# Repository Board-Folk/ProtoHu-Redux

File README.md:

# ProtoHu Redux

## A Simple flash HuCard for the NEC PC Engine/Turbo-Grafx range of consoles.

This project is based upon David Shadoff's [ProtoHu](https://github.com/dshadoff/ProtoHu_revA).
The original Eagle project was converted to KiCad. The most important
difference is the addition of an OR gate to fully decode the HuCard
address space, such that the image written to the flash is available
only in the lower half and not mirrored the the upper one. The
motivation for this is for the card to respond to the minimum practical
range of addresses in the HuCard space, freeing the upper region such
that diagnostic tests may be performed without risk of conflicts with
hardware in a real console. Specifically, this card can be flashed with
diagnostics for the CD hardware found in a PC Engine/Turb Duo system.

## PCB Production

The project consists of two boards: one that features the HuCard
connector and all the components, the other being a spacer to fit under
the first to give the complete assembly a flat lower surface. The upper
board should be 0.8mm thick with at least an ENIG finish for gold
plating on the edge connector contacts. A chamfered edge near the
connector will improve the fit.

The spacer board should be 1.6mm to clear the height of the components and
bring the total up to 2.4mm, which seems to be the nominal dimension of a
standard HuCard. As it contains no components, the finish on the spacer
boards is not important.

This visual design is intended to look vaguely like an original HuCard
when white solder mask is used with black silkscreen.

## BOM

| Reference  | Value          | Footprint |
|------------|----------------|-----------|
| C1,C3      | 0.1uF          | 0805      |
| C2         | 1uF            | 0805      |
| IC1        | SST39SF040     | SOP-32    |
| IC2        | 74HC32         | TSSOP-14  |
| J2         | 0.1" Header \* | DIP-32    |
| R1         | 47K            | 0805      |

\* It's possible to omit this and program the flash by holding the card 
firmly against some header pins mounted in your programming device.

## Assembly

Suggested order of operations:

* Populate IC1, IC2, then the passives and finally the header pins.
* Dry fit the two boards to test.
* When satisfied, use CA/super glue or similar to join the two boards. Some
  areas labeled "GLUE" are left unmasked to ensure direct adhesion to the
  board substrate, but glue can also be applied anywhere else you deem fit.

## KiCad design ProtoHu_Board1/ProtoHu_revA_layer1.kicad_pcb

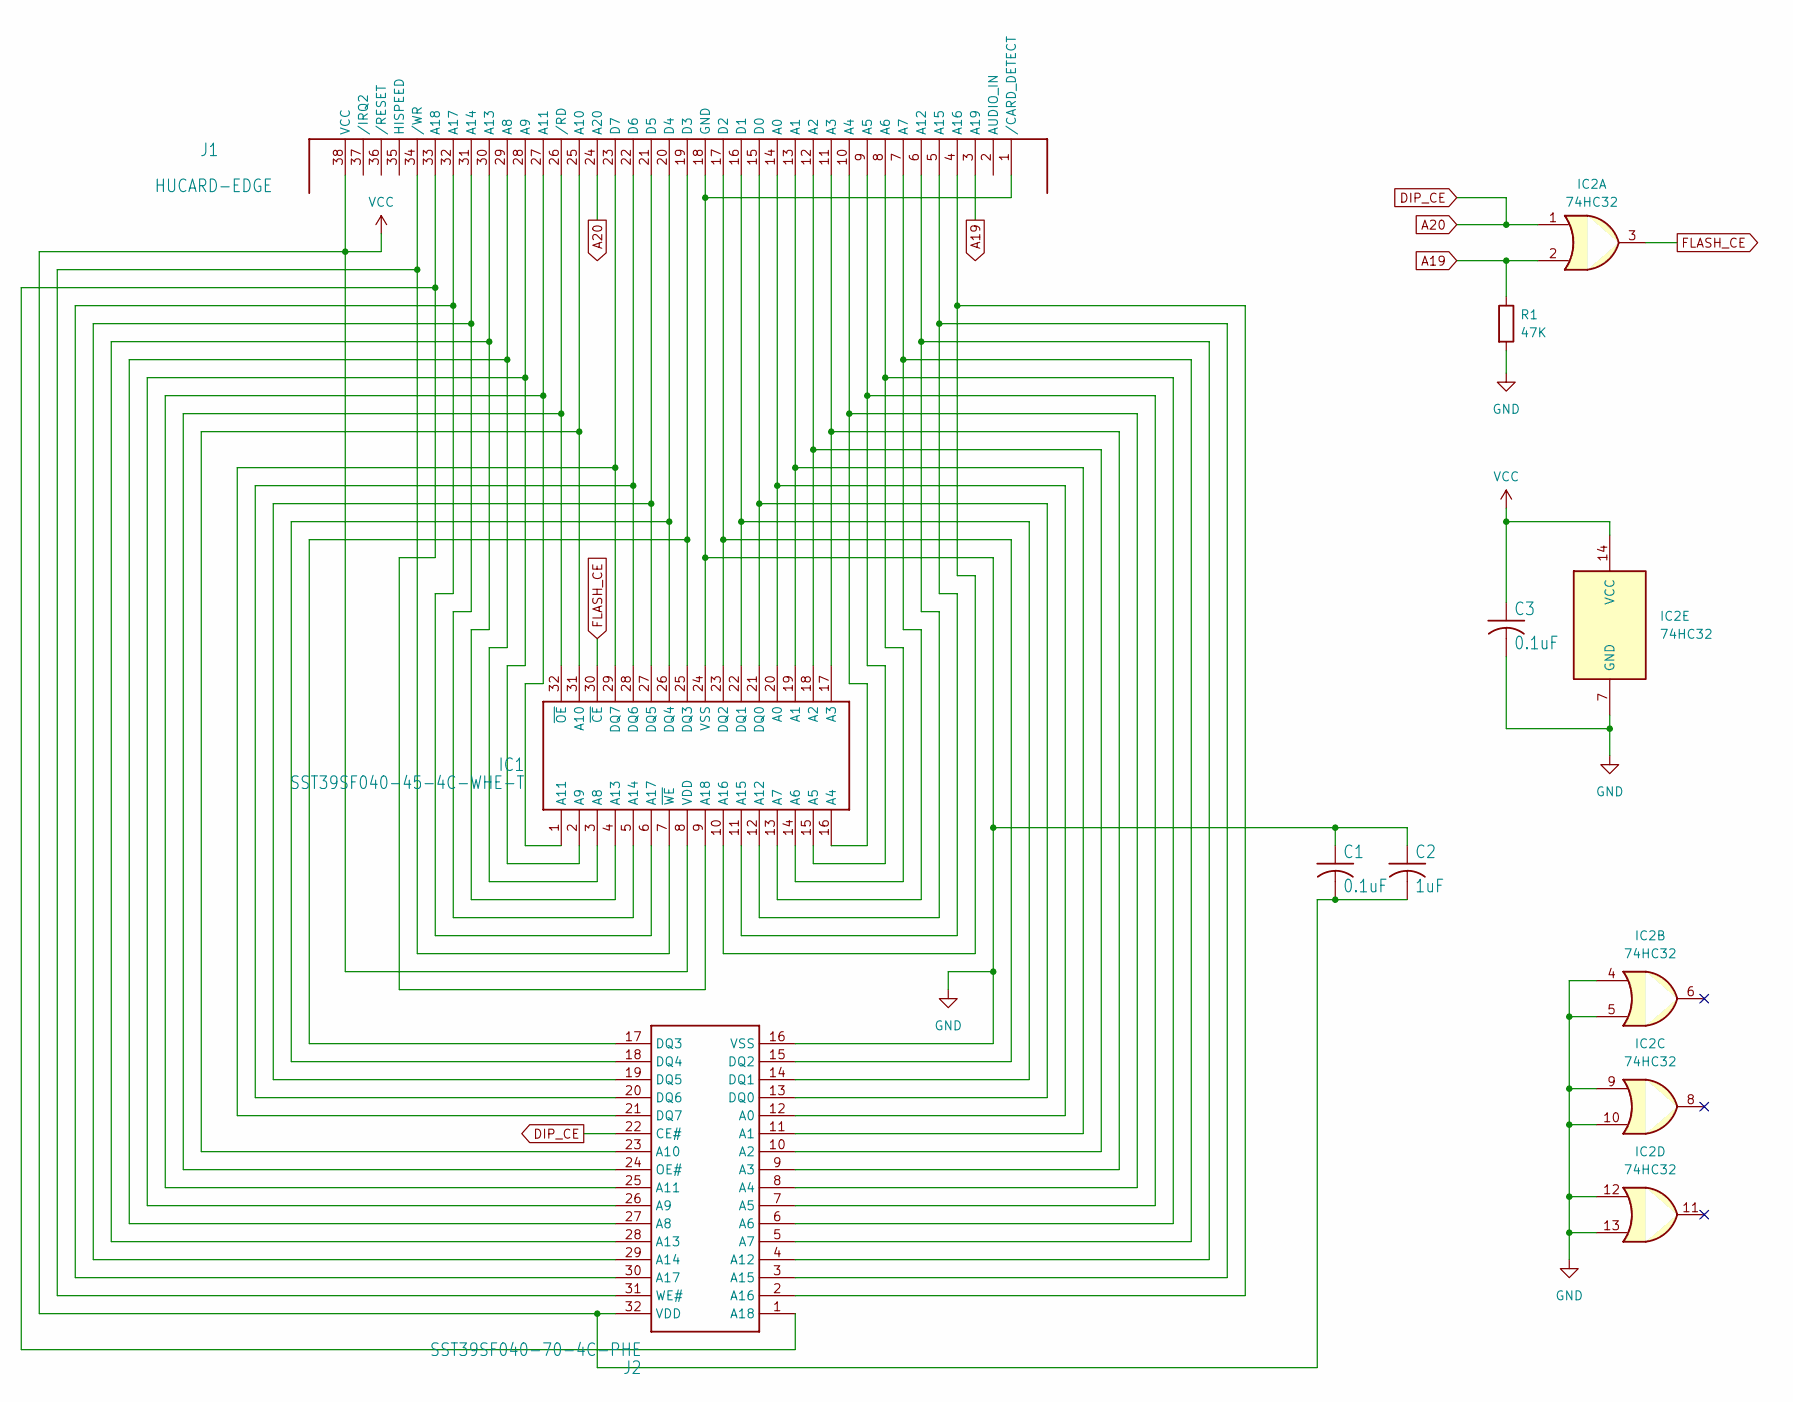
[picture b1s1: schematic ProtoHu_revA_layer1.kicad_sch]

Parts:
C1, C3: 0.1uF; R_0805_2012Metric
C2: 1uF; R_0805_2012Metric
IC1: SST39SF040-45-4C-WHE-T; SOP50P1400X120-32N
IC2: 74HC32; TSSOP-14_4.4x5mm_P0.65mm
J1: HUCARD-EDGE
J2: SST39SF040-70-4C-PHE; DIP1556W56P254L4191H508Q32N
R1: 47K; R_0805_2012Metric

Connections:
A19: IC2.2, J1.3 (A19), R1.1
A20: IC2.1, J1.24 (A20), J2.22 (CE#)
FLASH_CE: IC1.30 (~CE), IC2.3
GND: C1.1, C2.1, C3.2, IC1.24 (VSS), IC2.4, IC2.5, IC2.7 (GND), IC2.9, IC2.10, IC2.12, IC2.13, J1.1 (/CARD_DETECT), J1.18 (GND), J2.16 (VSS), R1.2
unnamed: IC1.20 (A0), J1.14 (A0), J2.12 (A0)
unnamed: IC1.19 (A1), J1.13 (A1), J2.11 (A1)
unnamed: IC1.18 (A2), J1.12 (A2), J2.10 (A2)
unnamed: IC1.17 (A3), J1.11 (A3), J2.9 (A3)
unnamed: IC1.16 (A4), J1.10 (A4), J2.8 (A4)
unnamed: IC1.15 (A5), J1.9 (A5), J2.7 (A5)
unnamed: IC1.14 (A6), J1.8 (A6), J2.6 (A6)
unnamed: IC1.13 (A7), J1.7 (A7), J2.5 (A7)
unnamed: IC1.3 (A8), J1.29 (A8), J2.27 (A8)
unnamed: IC1.2 (A9), J1.28 (A9), J2.26 (A9)
unnamed: IC1.31 (A10), J1.25 (A10), J2.23 (A10)
unnamed: IC1.1 (A11), J1.27 (A11), J2.25 (A11)
unnamed: IC1.12 (A12), J1.6 (A12), J2.4 (A12)
unnamed: IC1.4 (A13), J1.30 (A13), J2.28 (A13)
unnamed: IC1.5 (A14), J1.31 (A14), J2.29 (A14)
unnamed: IC1.11 (A15), J1.5 (A15), J2.3 (A15)
unnamed: IC1.10 (A16), J1.4 (A16), J2.2 (A16)
unnamed: IC1.6 (A17), J1.32 (A17), J2.30 (A17)
unnamed: IC1.9 (A18), J1.33 (A18), J2.1 (A18)
unnamed: IC1.21 (DQ0), J1.15 (D0), J2.13 (DQ0)
unnamed: IC1.22 (DQ1), J1.16 (D1), J2.14 (DQ1)
unnamed: IC1.23 (DQ2), J1.17 (D2), J2.15 (DQ2)
unnamed: IC1.25 (DQ3), J1.19 (D3), J2.17 (DQ3)
unnamed: IC1.26 (DQ4), J1.20 (D4), J2.18 (DQ4)
unnamed: IC1.27 (DQ5), J1.21 (D5), J2.19 (DQ5)
unnamed: IC1.28 (DQ6), J1.22 (D6), J2.20 (DQ6)
unnamed: IC1.29 (DQ7), J1.23 (D7), J2.21 (DQ7)
unnamed: IC1.32 (~OE), J1.26 (/RD), J2.24 (OE#)
unnamed: IC1.7 (~WE), J1.34 (/WR), J2.31 (WE#)
VCC: C1.2, C2.2, C3.1, IC1.8 (VDD), IC2.14 (VCC), J1.38 (VCC), J2.32 (VDD)

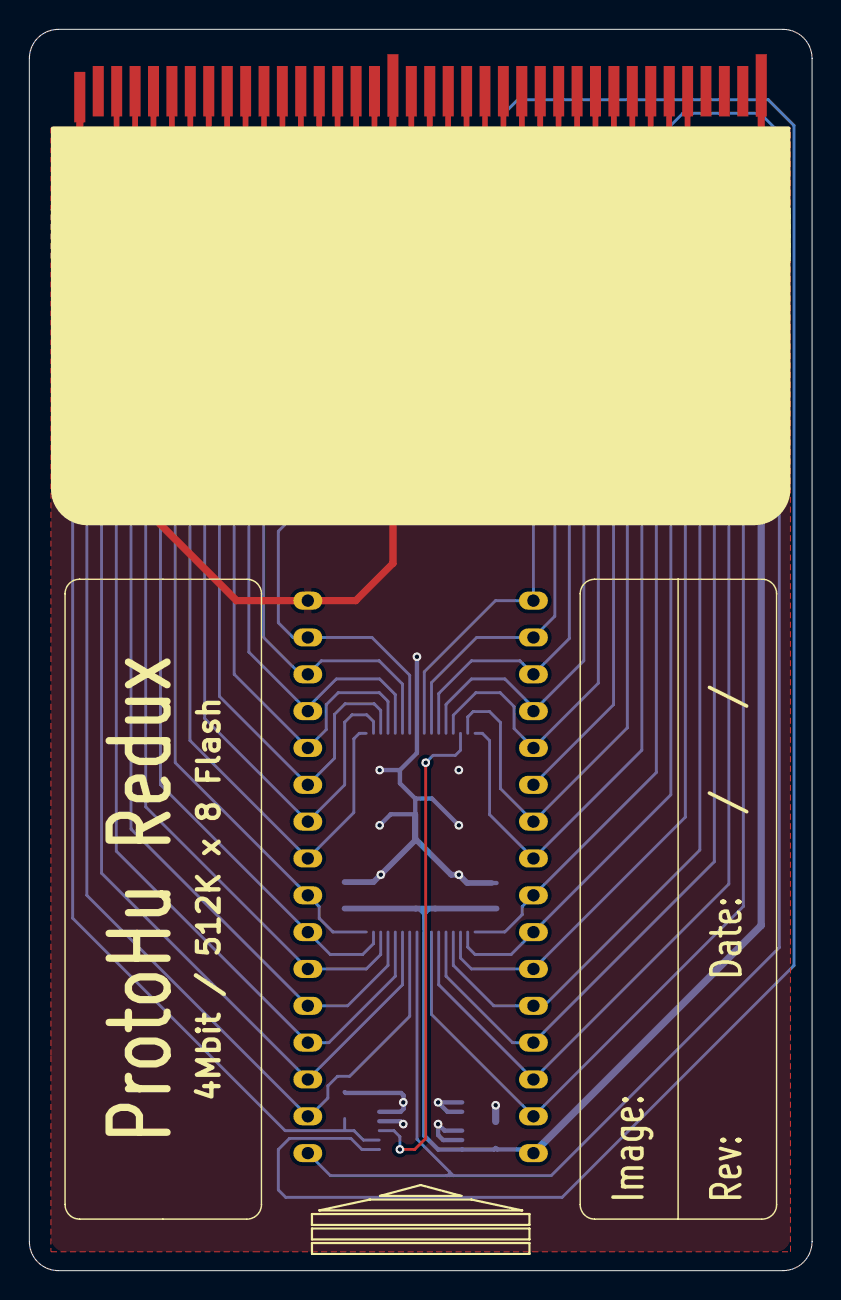
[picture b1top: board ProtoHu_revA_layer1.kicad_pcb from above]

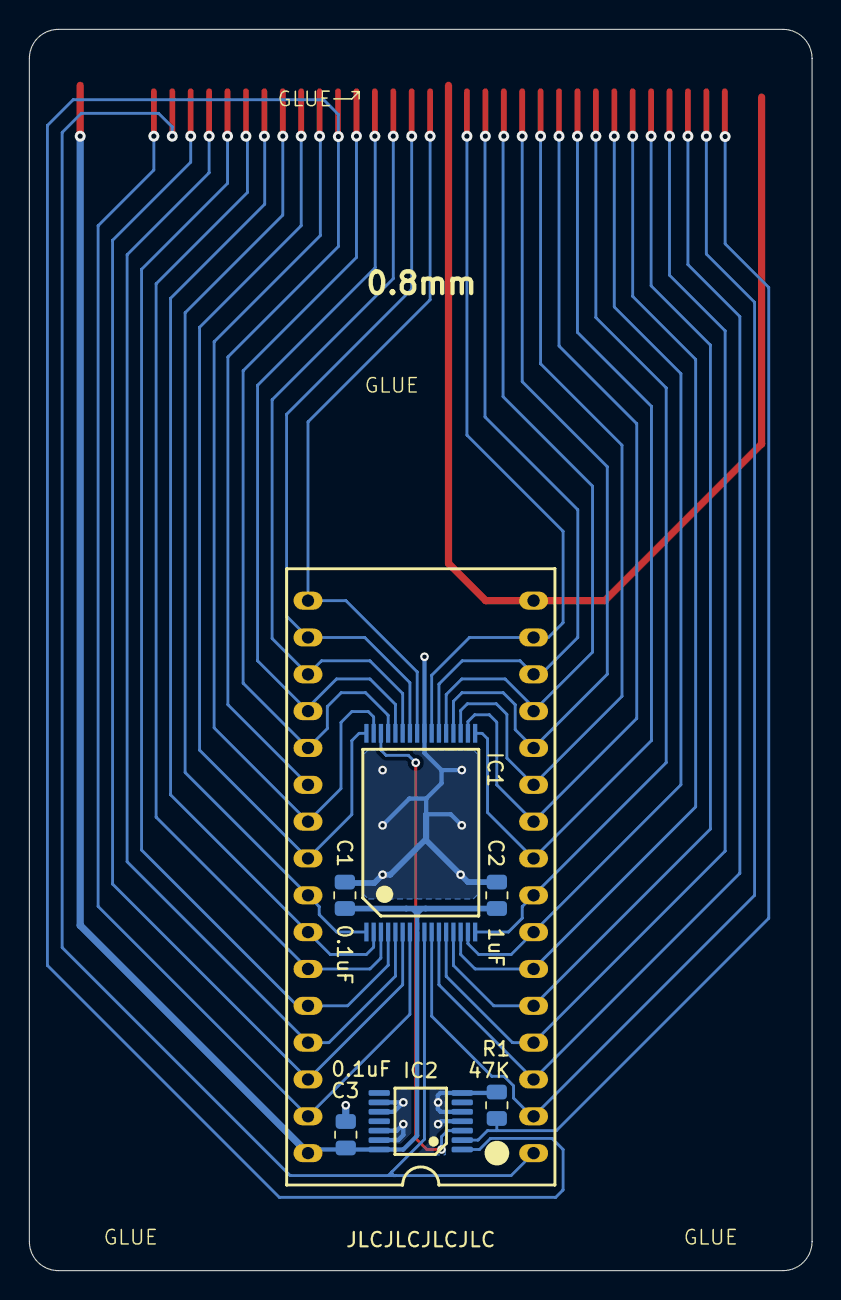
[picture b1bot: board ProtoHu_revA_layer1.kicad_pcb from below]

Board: 2 copper layers, 54.0 x 85.6 mm, 8 parts (7 on the bottom side), 34 nets.

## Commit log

2023-11-19 Real initial commit
2023-11-19 Add LICENSE
2023-11-19 Add README
2023-11-19 Fix pinout and part (LS -> HC) for IC2.
2023-11-19 Sync Gerbers for board 2.
2023-11-20 Correct Board 1 thickness hint on silkscreen.
2023-11-20 Move GLUE text out of solder mask area (fabs don't seem to want to print there).
2023-11-20 Add Assembly instructions to README.
2023-11-21 Add to PCB production section in README.
2025-04-29 Update to KiCad 9, fix solder mask arrow, update README.
